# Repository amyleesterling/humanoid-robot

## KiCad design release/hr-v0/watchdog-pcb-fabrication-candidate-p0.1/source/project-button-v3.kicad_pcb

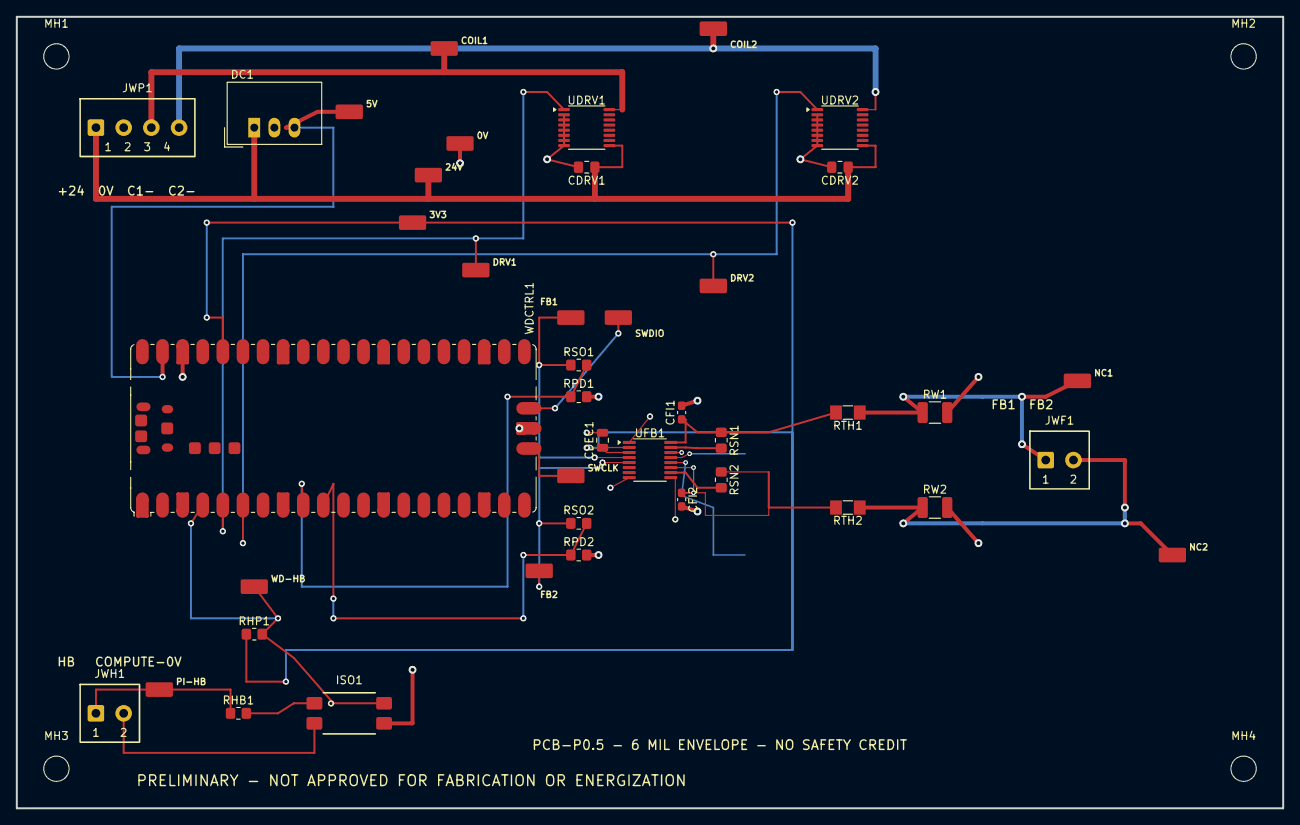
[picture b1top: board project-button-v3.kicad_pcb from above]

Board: 2 copper layers, 160.0 x 100.0 mm, 46 parts (0 on the bottom side), 24 nets.

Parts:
CDEC1: Murata GRM21BR71H104KA01L, 100 nF 50 V X7R 0805; C_0805_2012Metric
CDRV1, CDRV2: Murata GRM21BR71H104KA01L, 100 nF 50 V X7R 0805; C_0805_2012Metric_Pad1.18x1.45mm_HandSolder
CFI1, CFI2: TDK CGA3E2X7R1H103K080AA, 10 nF 50 V X7R 0603; C_0603_1608Metric_Pad1.08x0.95mm_HandSolder
DC1: TRACO POWER TSR 1-2450, 24 V to 5 V 1 A non-isola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; Converter_DCDC_TRACO_TSR-1_THT
ISO1: Vishay VO618A-4X017T heartbeat optocoupler; VO618A_Option7_SMD
JWF1: Phoenix Contact MKDS 1/2-3,5, item 1751248; MKDS_1_2_3P5
JWH1: Phoenix Contact MKDS 1/2-3,5, item 1751248; MKDS_1_2_3P5
JWP1: Phoenix Contact MKDS 1/4-3,5, item 1751264; MKDS_1_4_3P5
MH1, MH2, MH3, MH4: M3 BOARD-ONLY - MOUNTING/ENCLOSURE SELECTION OPEN; MountingHole_3.2mm_M3
RHB1: Panasonic ERJ6ENF9100V, 910 Ohm 1% 0805 0.125 W; R_0805_2012Metric_Pad1.20x1.40mm_HandSolder
RHP1: Panasonic ERJ6ENF1002V, 10.0 kOhm 1% 0805 0.125 W; R_0805_2012Metric_Pad1.20x1.40mm_HandSolder
RPD1, RPD2: Panasonic ERJ6ENF1002V, 10.0 kOhm 1% 0805; R_0805_2012Metric_Pad1.20x1.40mm_HandSolder
RSN1, RSN2: Panasonic ERJ6ENF5620V, 562 Ohm 1% 0805; R_0805_2012Metric_Pad1.20x1.40mm_HandSolder
RSO1, RSO2: Panasonic ERJ6ENF1001V, 1.00 kOhm 1% 0805; R_0805_2012Metric_Pad1.20x1.40mm_HandSolder
RTH1, RTH2: Vishay MMA02040C1001FB300, 1.00 kOhm 1% 0.4 W MELF; R_MiniMELF_MMA-0204
RW1, RW2: Vishay CRCW12102K70FKEA, 2.70 kOhm 1% 0.5 W 1210; R_1210_3225Metric_Pad1.30x2.65mm_HandSolder
TP1, TP2, TP3, TP4, TP5, TP6, TP7, TP8, TP9, TP10, TP11, TP12, TP13, TP14, TP15, TP16: Harwin S1751-46R SMT test point; Harwin_S1751_46R
UDRV1: Texas Instruments TPL7407LPWR channel-1 relay dri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; TSSOP-16_4.4x5mm_P0.65mm
UDRV2: Texas Instruments TPL7407LPWR channel-2 relay dri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; TSSOP-16_4.4x5mm_P0.65mm
UFB1: Texas Instruments ISO1212DBQ dual 24 V input rece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; SSOP-16_3.9x4.9mm_P0.635mm
WDCTRL1: Raspberry Pi Pico 1, order SC0915 / RP2040; RaspberryPi_Pico_SMD

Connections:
COMPUTE_0V: ISO1.2, JWH1.2
FB_IN1: RSN1.2, UFB1.15
FB_IN2: RSN2.2, UFB1.10
FB_SENSE1: CFI1.1, RSN1.1, RTH1.2, UFB1.16
FB_SENSE2: CFI2.1, RSN2.1, RTH2.2, UFB1.11
HB_LED_A: ISO1.1, RHB1.2
PI_HEARTBEAT: JWH1.1, RHB1.1, TP5.1
SAFETY_0V: CDEC1.2, CDRV1.2, CDRV2.2, CFI1.2, CFI2.2, DC1.2, ISO1.3, JWP1.2, RPD1.2, RPD2.2, RW1.2, RW2.2, TP2.1, UDRV1.2, UDRV1.3, UDRV1.4, UDRV1.5, UDRV1.6, UDRV1.7, UDRV1.8, UDRV2.2, UDRV2.3, UDRV2.4, UDRV2.5, UDRV2.6, UDRV2.7, UDRV2.8, UFB1.1, UFB1.8, UFB1.9, UFB1.14, WDCTRL1.38, WDCTRL1.D2
SAFETY_24V: CDRV1.1, CDRV2.1, DC1.1, JWP1.1, TP1.1, UDRV1.9, UDRV2.9
UFB_OUT1: RSO1.1, TP13.1, UFB1.4
UFB_OUT2: RSO2.1, TP14.1, UFB1.5
WD1_COIL_N: JWP1.3, TP9.1, UDRV1.16
WD1_DRIVE: TP7.1, UDRV1.1, WDCTRL1.5
WD1_NC_24V: JWF1.1, RTH1.1, RW1.1, TP11.1
WD1_NC_DIAG: RPD1.1, RSO1.2, WDCTRL1.9
WD2_COIL_N: JWP1.4, TP10.1, UDRV2.16
WD2_DRIVE: TP8.1, UDRV2.1, WDCTRL1.6
WD2_NC_24V: JWF1.2, RTH2.1, RW2.1, TP12.1
WD2_NC_DIAG: RPD2.1, RSO2.2, WDCTRL1.10
WD_3V3: CDEC1.1, RHP1.1, TP4.1, UFB1.2, UFB1.3, WDCTRL1.36
WD_5V: DC1.3, TP3.1, WDCTRL1.39
WD_HEARTBEAT: ISO1.4, RHP1.2, TP6.1, WDCTRL1.4
WD_SWCLK: TP16.1, WDCTRL1.D1
WD_SWDIO: TP15.1, WDCTRL1.D3

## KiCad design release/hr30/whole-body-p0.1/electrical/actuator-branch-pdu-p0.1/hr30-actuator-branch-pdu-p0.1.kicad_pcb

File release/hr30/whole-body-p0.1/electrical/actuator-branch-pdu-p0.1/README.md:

# HR-30 actuator branch PDU P0.1

**PRELIMINARY - NOT APPROVED FOR PROCUREMENT, FABRICATION, ASSEMBLY, CONNECTION, POWERED TESTING, MOTION OR ENERGIZATION**

This package provides one editable six-channel native KiCad schematic and routed 124 x 45 mm ten-layer PCB candidate. Five distributed assembly instances allocate 25 whole-body actuator branches and retain five DNP spares. KiCad verifies schematic ERC 0/0, PCB DRC 0/0 and zero unconnected pads. The route separates shared input, individual outputs and six control-net families; exact production stackup, copper weight, DFM, thermal rise and physical tests remain open. It is a restrained commissioning architecture only; reverse energy, connector closure, dynamic torque and all work authority remain open.

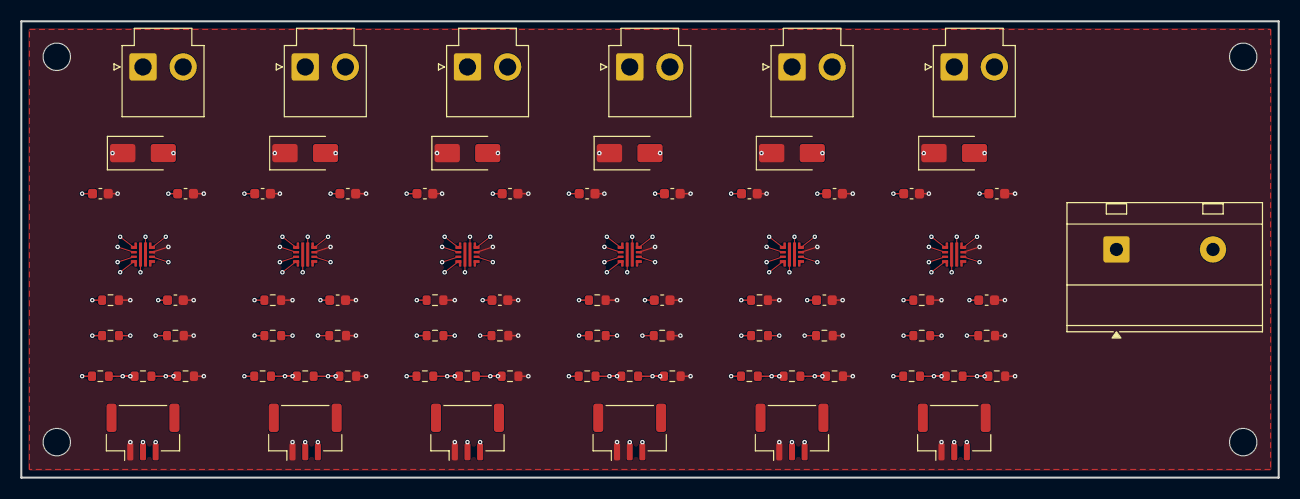
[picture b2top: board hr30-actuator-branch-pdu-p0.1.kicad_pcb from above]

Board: 10 copper layers, 124.0 x 45.0 mm, 83 parts (0 on the bottom side), 44 nets.

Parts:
C101, C201, C301, C401, C501, C601: 1uF 25V X7R input; C_0603_1608Metric
C102, C202, C302, C402, C502, C602: 2x1uF 25V X7R output equivalent; C_0603_1608Metric
C103, C203, C303, C403, C503, C603: 3.3nF dVdt; C_0603_1608Metric
D101, D201, D301, D401, D501, D601: LOCAL BRANCH CLAMP - DNP; D_SMA
J1: 12 V CONTROLLED INPUT; TerminalBlock_MetzConnect_Type703_RT10N02HGLU_1x02_P9.52mm_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
J101: CHANNEL 1 OUTPUT; JST_VH_B2P-VH_1x02_P3.96mm_Vertical
J102: CHANNEL 2 OUTPUT; JST_VH_B2P-VH_1x02_P3.96mm_Vertical
J103: CHANNEL 3 OUTPUT; JST_VH_B2P-VH_1x02_P3.96mm_Vertical
J104: CHANNEL 4 OUTPUT; JST_VH_B2P-VH_1x02_P3.96mm_Vertical
J105: CHANNEL 5 OUTPUT; JST_VH_B2P-VH_1x02_P3.96mm_Vertical
J106: CHANNEL 6 OUTPUT; JST_VH_B2P-VH_1x02_P3.96mm_Vertical
J201: CHANNEL 1 CONTROL; JST_GH_BM03B-GHS-TBT_1x03-1MP_P1.25mm_Vertical
J202: CHANNEL 2 CONTROL; JST_GH_BM03B-GHS-TBT_1x03-1MP_P1.25mm_Vertical
J203: CHANNEL 3 CONTROL; JST_GH_BM03B-GHS-TBT_1x03-1MP_P1.25mm_Vertical
J204: CHANNEL 4 CONTROL; JST_GH_BM03B-GHS-TBT_1x03-1MP_P1.25mm_Vertical
J205: CHANNEL 5 CONTROL; JST_GH_BM03B-GHS-TBT_1x03-1MP_P1.25mm_Vertical
J206: CHANNEL 6 CONTROL; JST_GH_BM03B-GHS-TBT_1x03-1MP_P1.25mm_Vertical
MH1, MH2, MH3, MH4: M2.5 BOARD-ONLY; MountingHole_2.7mm_M2.5
R101, R201, R301, R401, R501, R601: 470k 1% UVLO top; R_0603_1608Metric
R102, R202, R302, R402, R502, R602: 27.4k 1% UVLO/OVLO middle; R_0603_1608Metric
R103, R203, R303, R403, R503, R603: 40.2k 1% OVLO bottom; R_0603_1608Metric
R104, R204, R304, R404, R504, R604: 47k 1% PGTH top; R_0603_1608Metric
R105, R205, R305, R405, R505, R605: 5.76k 1% PGTH bottom; R_0603_1608Metric
R106, R206, R306, R406, R506, R606: ASSEMBLY VARIANT RILM; R_0603_1608Metric
U201, U202, U203, U204, U205, U206: TPS259474LRPWR circuit-breaker latch-off eFuse; TI_RPW0010A_HotRodQFN_2x2mm_P0.45mm_TI4225183A_P02

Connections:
BRANCH_1_12V: C102.1, D101.2, J101.2, R104.1, U201.6
BRANCH_2_12V: C202.1, D201.2, J102.2, R204.1, U202.6
BRANCH_3_12V: C302.1, D301.2, J103.2, R304.1, U203.6
BRANCH_4_12V: C402.1, D401.2, J104.2, R404.1, U204.6
BRANCH_5_12V: C502.1, D501.2, J105.2, R504.1, U205.6
BRANCH_6_12V: C602.1, D601.2, J106.2, R604.1, U206.6
CH1_DVDT: C103.1, U201.7
CH1_EN: J201.2, R101.2, R102.1, U201.1
CH1_ILM: R106.1, U201.9
CH1_OV: R102.2, R103.1, U201.2
CH1_PG: J201.3, U201.3
CH1_PGTH: R104.2, R105.1, U201.4
CH2_DVDT: C203.1, U202.7
CH2_EN: J202.2, R201.2, R202.1, U202.1
CH2_ILM: R206.1, U202.9
CH2_OV: R202.2, R203.1, U202.2
CH2_PG: J202.3, U202.3
CH2_PGTH: R204.2, R205.1, U202.4
CH3_DVDT: C303.1, U203.7
CH3_EN: J203.2, R301.2, R302.1, U203.1
CH3_ILM: R306.1, U203.9
CH3_OV: R302.2, R303.1, U203.2
CH3_PG: J203.3, U203.3
CH3_PGTH: R304.2, R305.1, U203.4
CH4_DVDT: C403.1, U204.7
CH4_EN: J204.2, R401.2, R402.1, U204.1
CH4_ILM: R406.1, U204.9
CH4_OV: R402.2, R403.1, U204.2
CH4_PG: J204.3, U204.3
CH4_PGTH: R404.2, R405.1, U204.4
CH5_DVDT: C503.1, U205.7
CH5_EN: J205.2, R501.2, R502.1, U205.1
CH5_ILM: R506.1, U205.9
CH5_OV: R502.2, R503.1, U205.2
CH5_PG: J205.3, U205.3
CH5_PGTH: R504.2, R505.1, U205.4
CH6_DVDT: C603.1, U206.7
CH6_EN: J206.2, R601.2, R602.1, U206.1
CH6_ILM: R606.1, U206.9
CH6_OV: R602.2, R603.1, U206.2
CH6_PG: J206.3, U206.3
CH6_PGTH: R604.2, R605.1, U206.4
PDU_0V: C101.2, C102.2, C103.2, C201.2, C202.2, C203.2, C301.2, C302.2, C303.2, C401.2, C402.2, C403.2, C501.2, C502.2, C503.2, C601.2, C602.2, C603.2, D101.1, D201.1, D301.1, D401.1, D501.1, D601.1, J1.1, J101.1, J102.1, J103.1, J104.1, J105.1, J106.1, J201.1, J202.1, J203.1, J204.1, J205.1, J206.1, R103.2, R105.2, R106.2, R203.2, R205.2, R206.2, R303.2, R305.2, R306.2, R403.2, R405.2, R406.2, R503.2, R505.2, R506.2, R603.2, R605.2, R606.2, U201.8, U202.8, U203.8, U204.8, U205.8, U206.8
PDU_12V_IN: C101.1, C201.1, C301.1, C401.1, C501.1, C601.1, J1.2, R101.1, R201.1, R301.1, R401.1, R501.1, R601.1, U201.5, U202.5, U203.5, U204.5, U205.5, U206.5

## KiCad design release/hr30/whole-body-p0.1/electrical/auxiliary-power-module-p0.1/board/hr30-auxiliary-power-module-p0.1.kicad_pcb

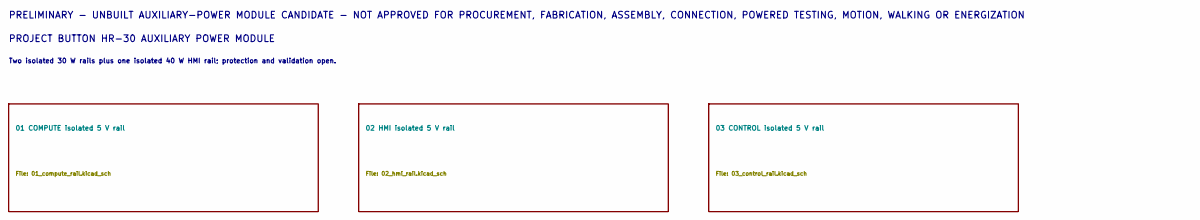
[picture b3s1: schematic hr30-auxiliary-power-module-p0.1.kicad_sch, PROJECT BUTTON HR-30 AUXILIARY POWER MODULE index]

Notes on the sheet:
PRELIMINARY - UNBUILT AUXILIARY-POWER MODULE CANDIDATE - NOT APPROVED FOR PROCUREMENT, FABRICATION, ASSEMBLY, CONNECTION, POWERED TESTING, MOTION, WALKING OR ENERGIZATION
PROJECT BUTTON HR-30 AUXILIARY POWER MODULE
Two isolated 30 W rails plus one isolated 40 W HMI rail; protection and validation open.

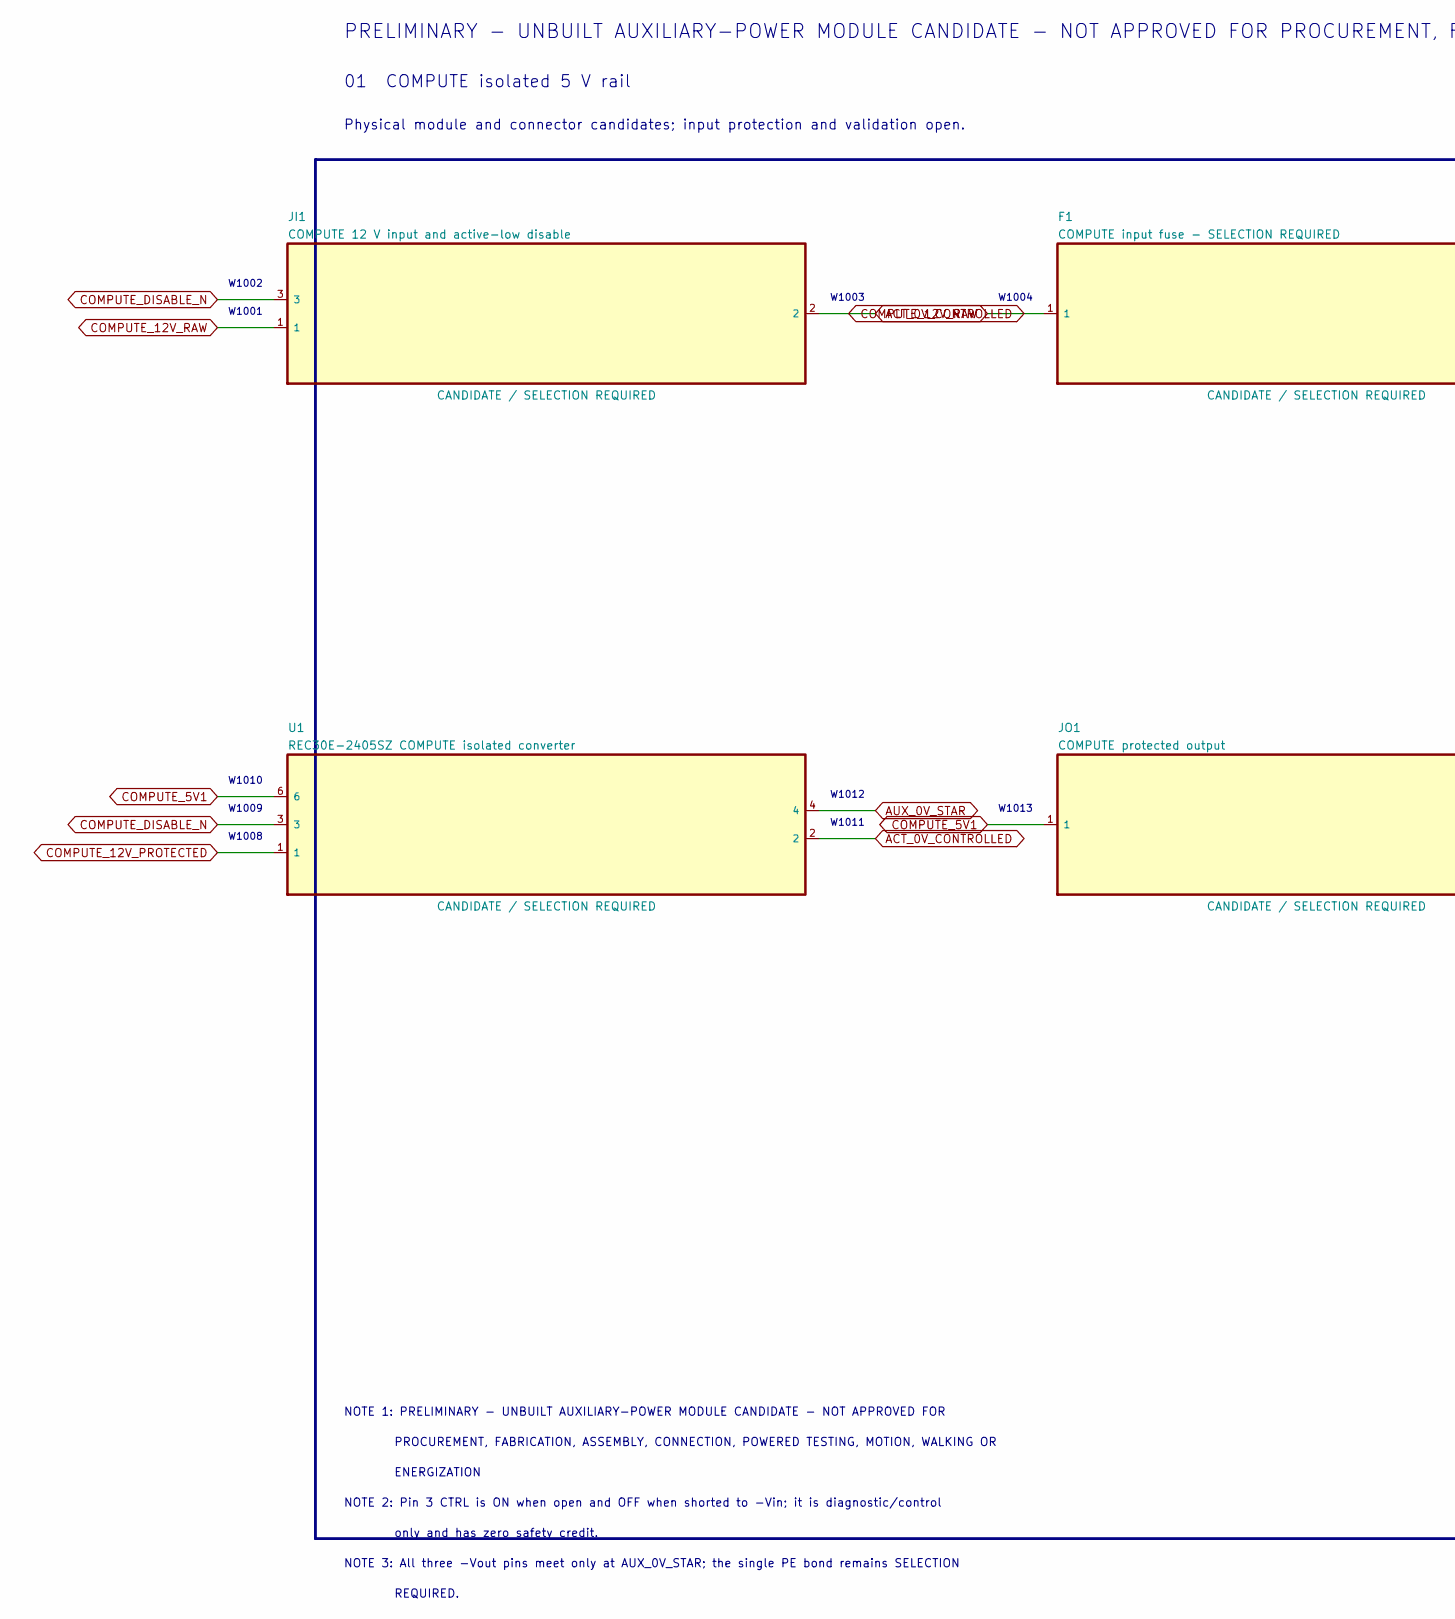
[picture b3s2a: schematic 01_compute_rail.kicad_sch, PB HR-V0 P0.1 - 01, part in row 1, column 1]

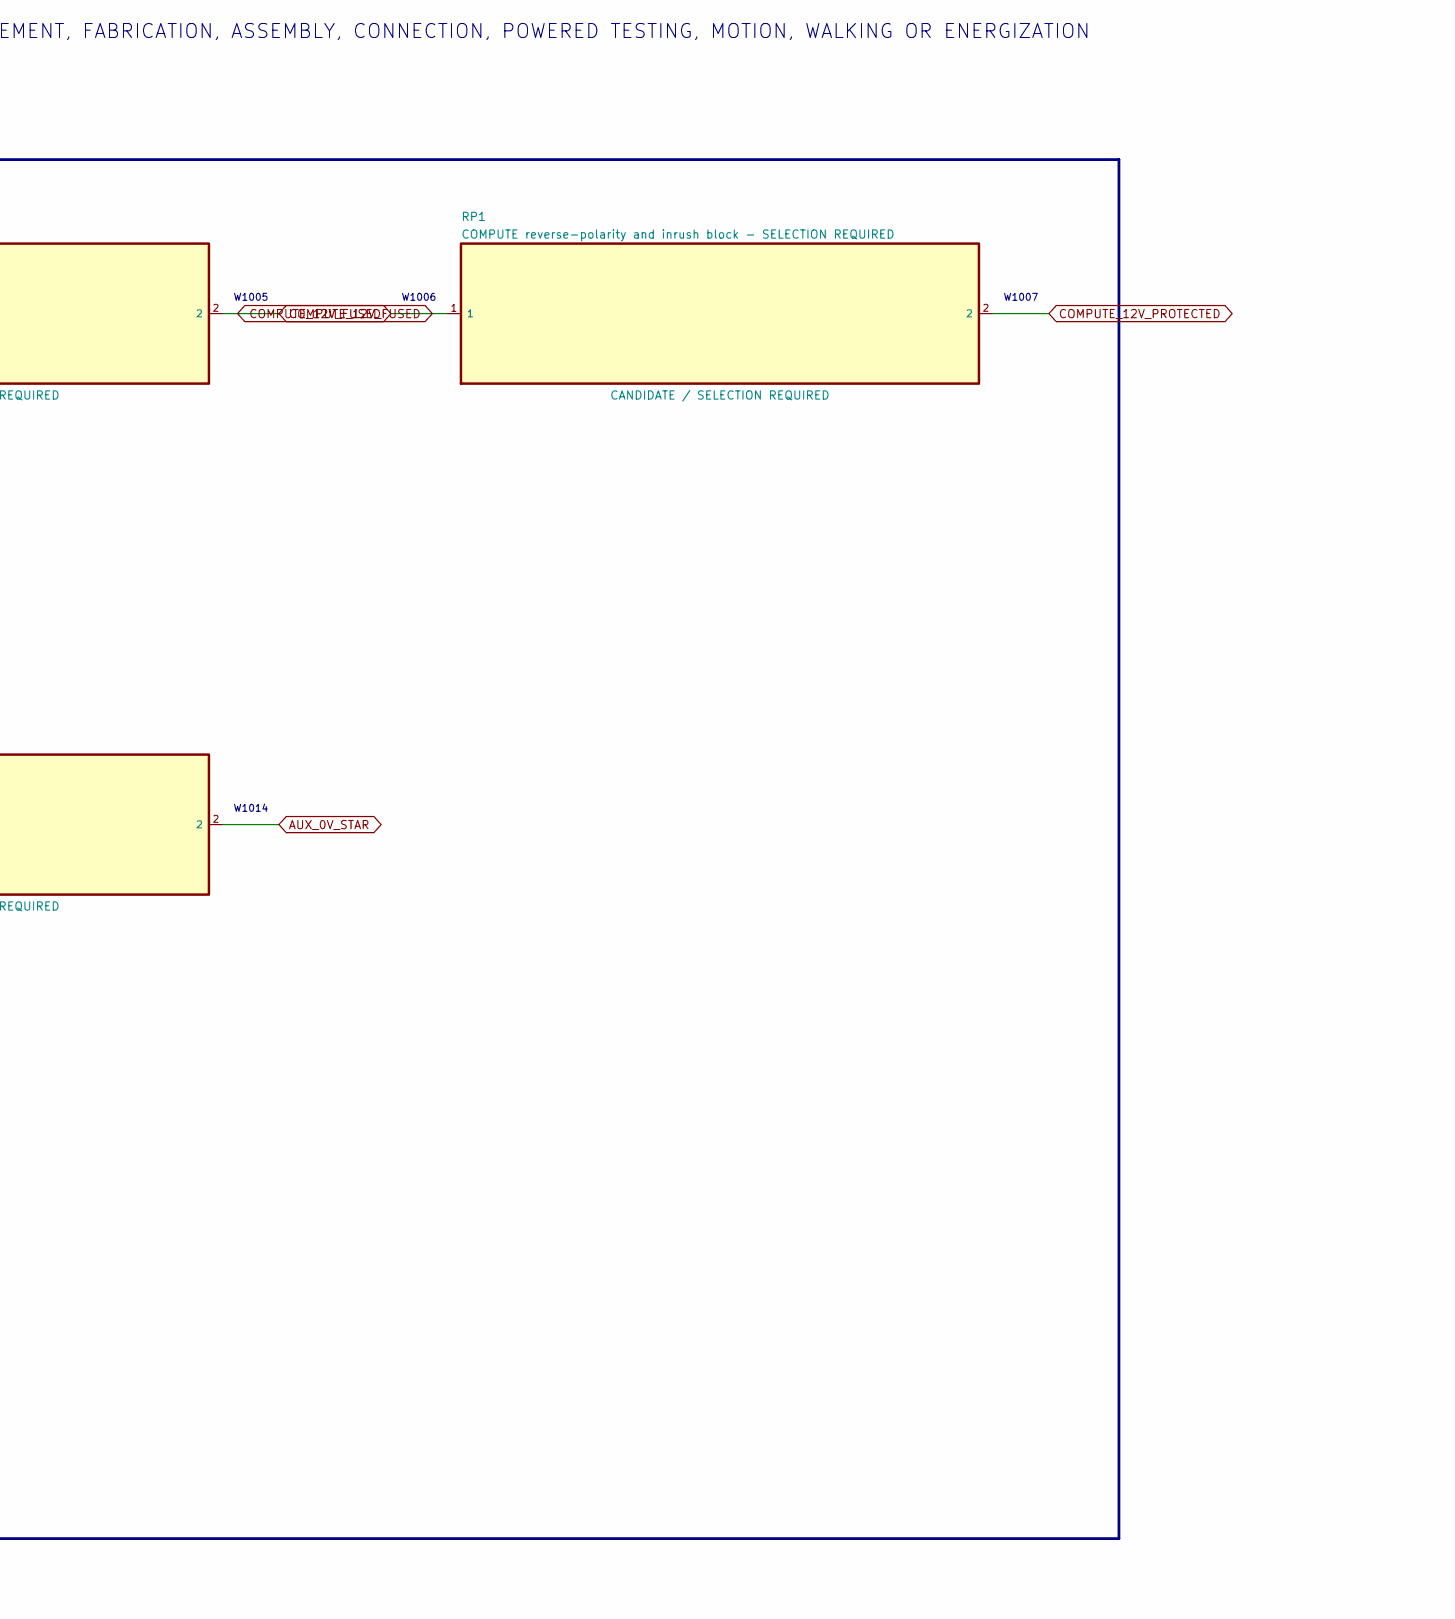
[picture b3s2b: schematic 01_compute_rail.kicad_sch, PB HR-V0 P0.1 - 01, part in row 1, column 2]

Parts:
F1: COMPUTE input fuse - SELECTION REQUIRED; AUX_SELECTION_BLOCK
JI1: COMPUTE 12 V input and active-low disable; JST_VH_B3P-VH-B_1x03_P3.96mm_Vertical
JO1: COMPUTE protected output; JST_VH_B2P-VH-B_1x02_P3.96mm_Vertical
RP1: COMPUTE reverse-polarity and inrush block - SELEC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; AUX_SELECTION_BLOCK
U1: REC30E-2405SZ COMPUTE isolated converter; REC30E-Z

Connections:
ACT_0V_CONTROLLED: JI1.2, U1.2; also elsewhere on the board
AUX_0V_STAR: JO1.2, U1.4; also elsewhere on the board
COMPUTE_5V1: JO1.1, U1.6
COMPUTE_12V_FUSED: F1.2, RP1.1
COMPUTE_12V_PROTECTED: RP1.2, U1.1
COMPUTE_12V_RAW: F1.1, JI1.1
COMPUTE_DISABLE_N: JI1.3, U1.3

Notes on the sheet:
PRELIMINARY - UNBUILT AUXILIARY-POWER MODULE CANDIDATE - NOT APPROVED FOR PROCUREMENT, FABRICATION, ASSEMBLY, CONNECTION, POWERED TESTING, MOTION, WALKING OR ENERGIZATION
01 COMPUTE isolated 5 V rail
Physical module and connector candidates; input protection and validation open.
W1001
W1002
W1003
W1004
W1005
W1006
W1007
W1008
W1009
W1010
W1011
W1012
W1013
W1014
NOTE 1: PRELIMINARY - UNBUILT AUXILIARY-POWER MODULE CANDIDATE - NOT APPROVED FOR
PROCUREMENT, FABRICATION, ASSEMBLY, CONNECTION, POWERED TESTING, MOTION, WALKING OR
ENERGIZATION
NOTE 2: Pin 3 CTRL is ON when open and OFF when shorted to -Vin; it is diagnostic/control
only and has zero safety credit.
NOTE 3: All three -Vout pins meet only at AUX_0V_STAR; the single PE bond remains SELECTION
REQUIRED.

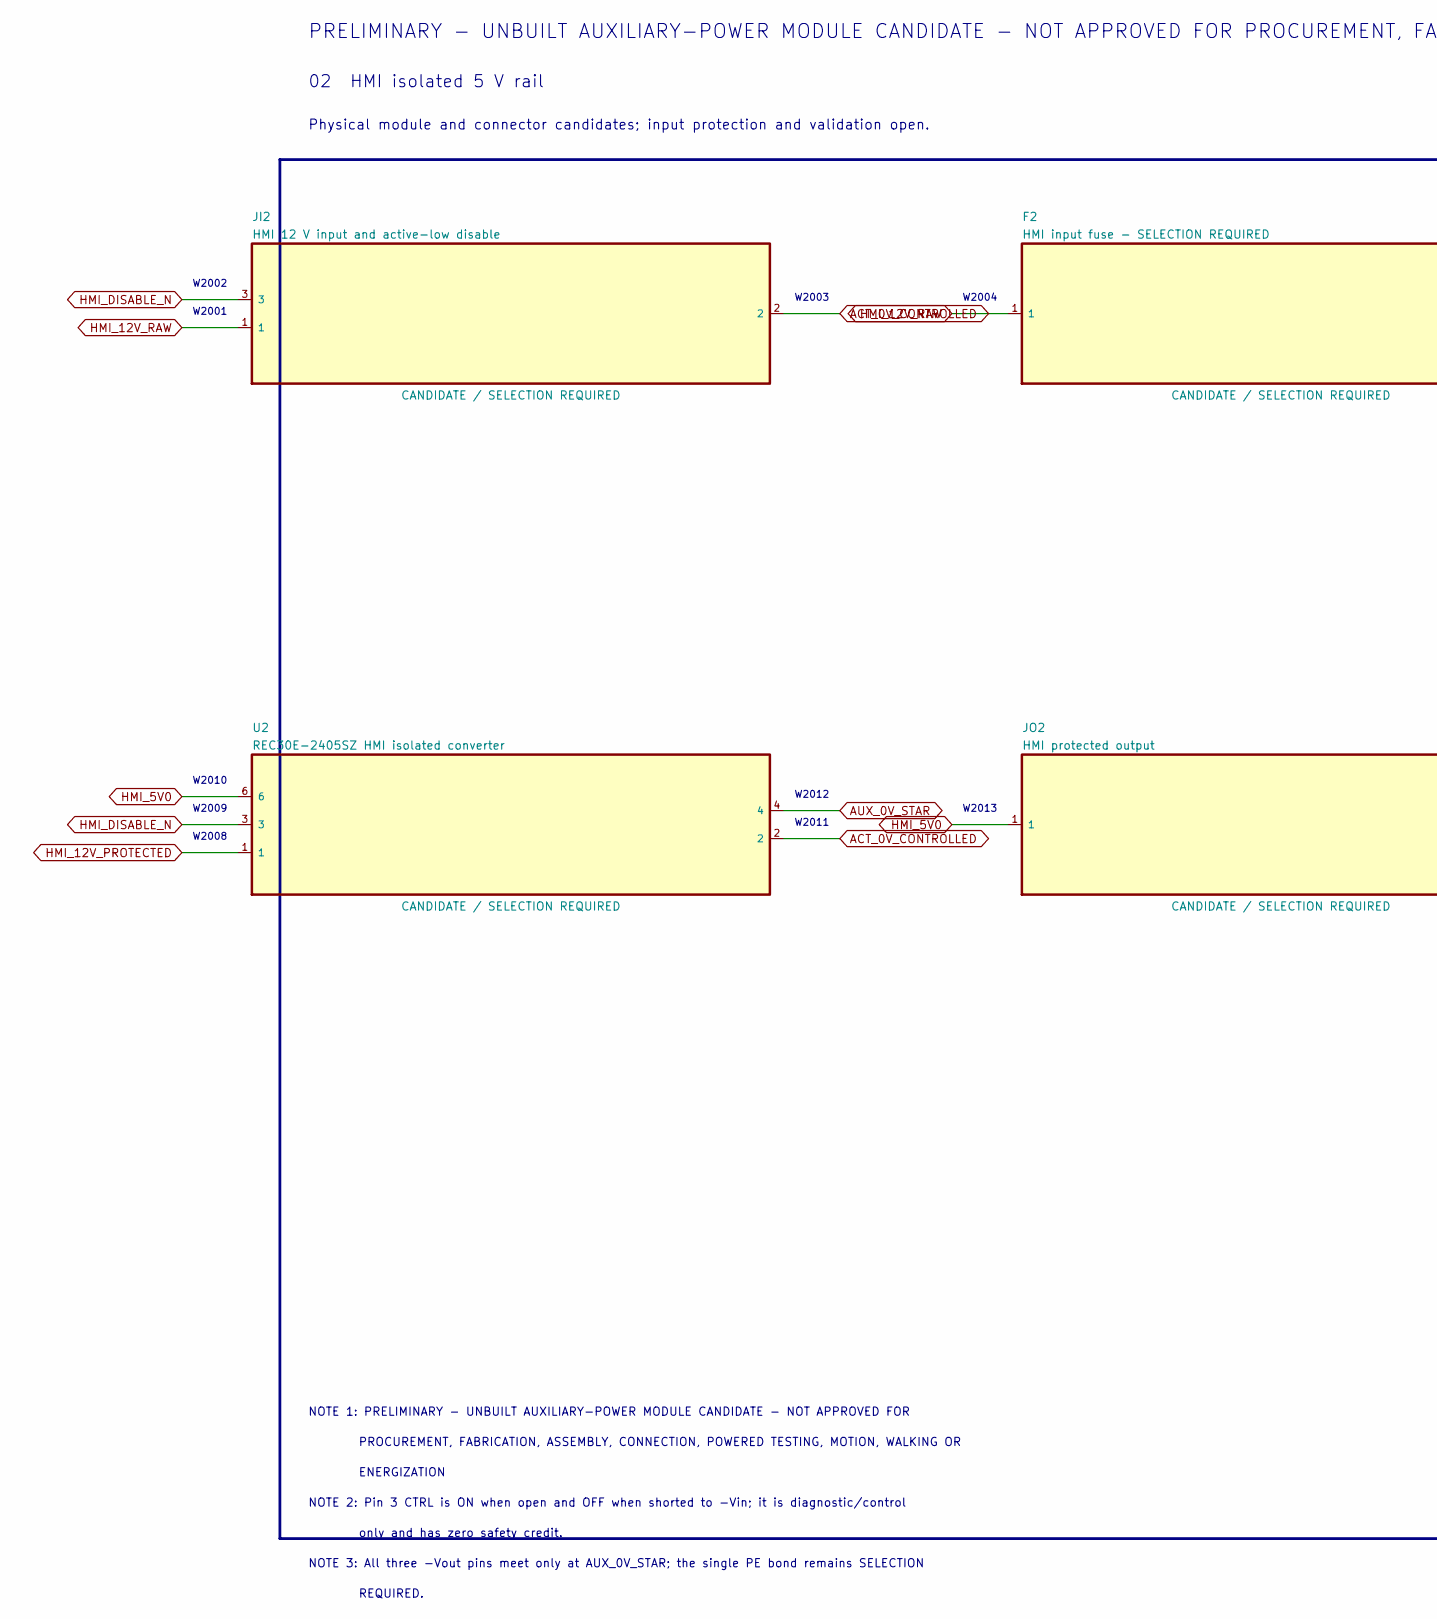
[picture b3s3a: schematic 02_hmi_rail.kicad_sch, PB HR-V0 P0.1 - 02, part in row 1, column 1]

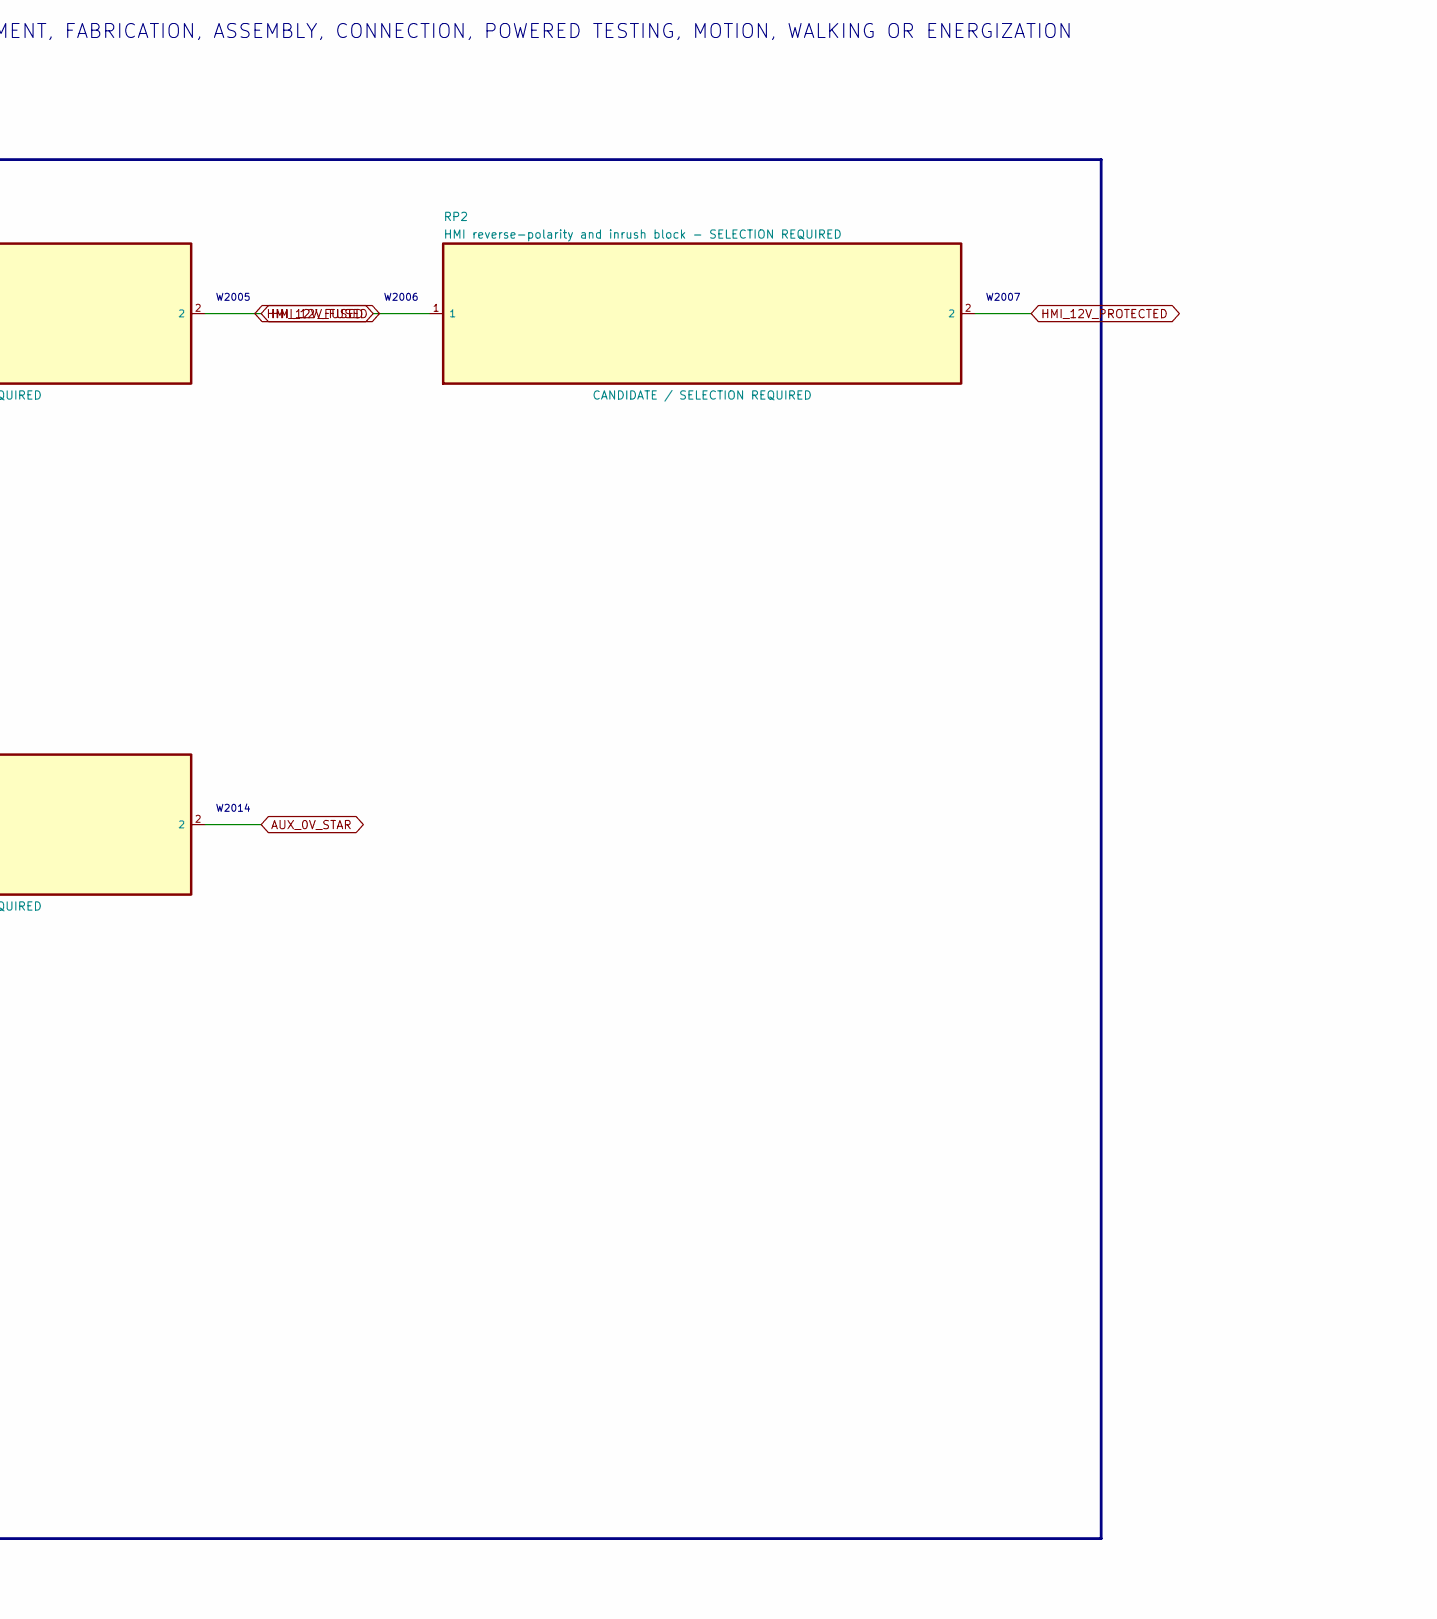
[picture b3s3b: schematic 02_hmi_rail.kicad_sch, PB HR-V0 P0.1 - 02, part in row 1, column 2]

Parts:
F2: HMI input fuse - SELECTION REQUIRED; AUX_SELECTION_BLOCK
JI2: HMI 12 V input and active-low disable; JST_VH_B3P-VH-B_1x03_P3.96mm_Vertical
JO2: HMI protected output; JST_VH_B2P-VH-B_1x02_P3.96mm_Vertical
RP2: HMI reverse-polarity and inrush block - SELECTION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; AUX_SELECTION_BLOCK
U2: REC30E-2405SZ HMI isolated converter; REC30E-Z

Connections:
ACT_0V_CONTROLLED: JI2.2, U2.2; also elsewhere on the board
AUX_0V_STAR: JO2.2, U2.4; also elsewhere on the board
HMI_5V0: JO2.1, U2.6
HMI_12V_FUSED: F2.2, RP2.1
HMI_12V_PROTECTED: RP2.2, U2.1
HMI_12V_RAW: F2.1, JI2.1
HMI_DISABLE_N: JI2.3, U2.3

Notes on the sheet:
PRELIMINARY - UNBUILT AUXILIARY-POWER MODULE CANDIDATE - NOT APPROVED FOR PROCUREMENT, FABRICATION, ASSEMBLY, CONNECTION, POWERED TESTING, MOTION, WALKING OR ENERGIZATION
02 HMI isolated 5 V rail
Physical module and connector candidates; input protection and validation open.
W2001
W2002
W2003
W2004
W2005
W2006
W2007
W2008
W2009
W2010
W2011
W2012
W2013
W2014
NOTE 1: PRELIMINARY - UNBUILT AUXILIARY-POWER MODULE CANDIDATE - NOT APPROVED FOR
PROCUREMENT, FABRICATION, ASSEMBLY, CONNECTION, POWERED TESTING, MOTION, WALKING OR
ENERGIZATION
NOTE 2: Pin 3 CTRL is ON when open and OFF when shorted to -Vin; it is diagnostic/control
only and has zero safety credit.
NOTE 3: All three -Vout pins meet only at AUX_0V_STAR; the single PE bond remains SELECTION
REQUIRED.

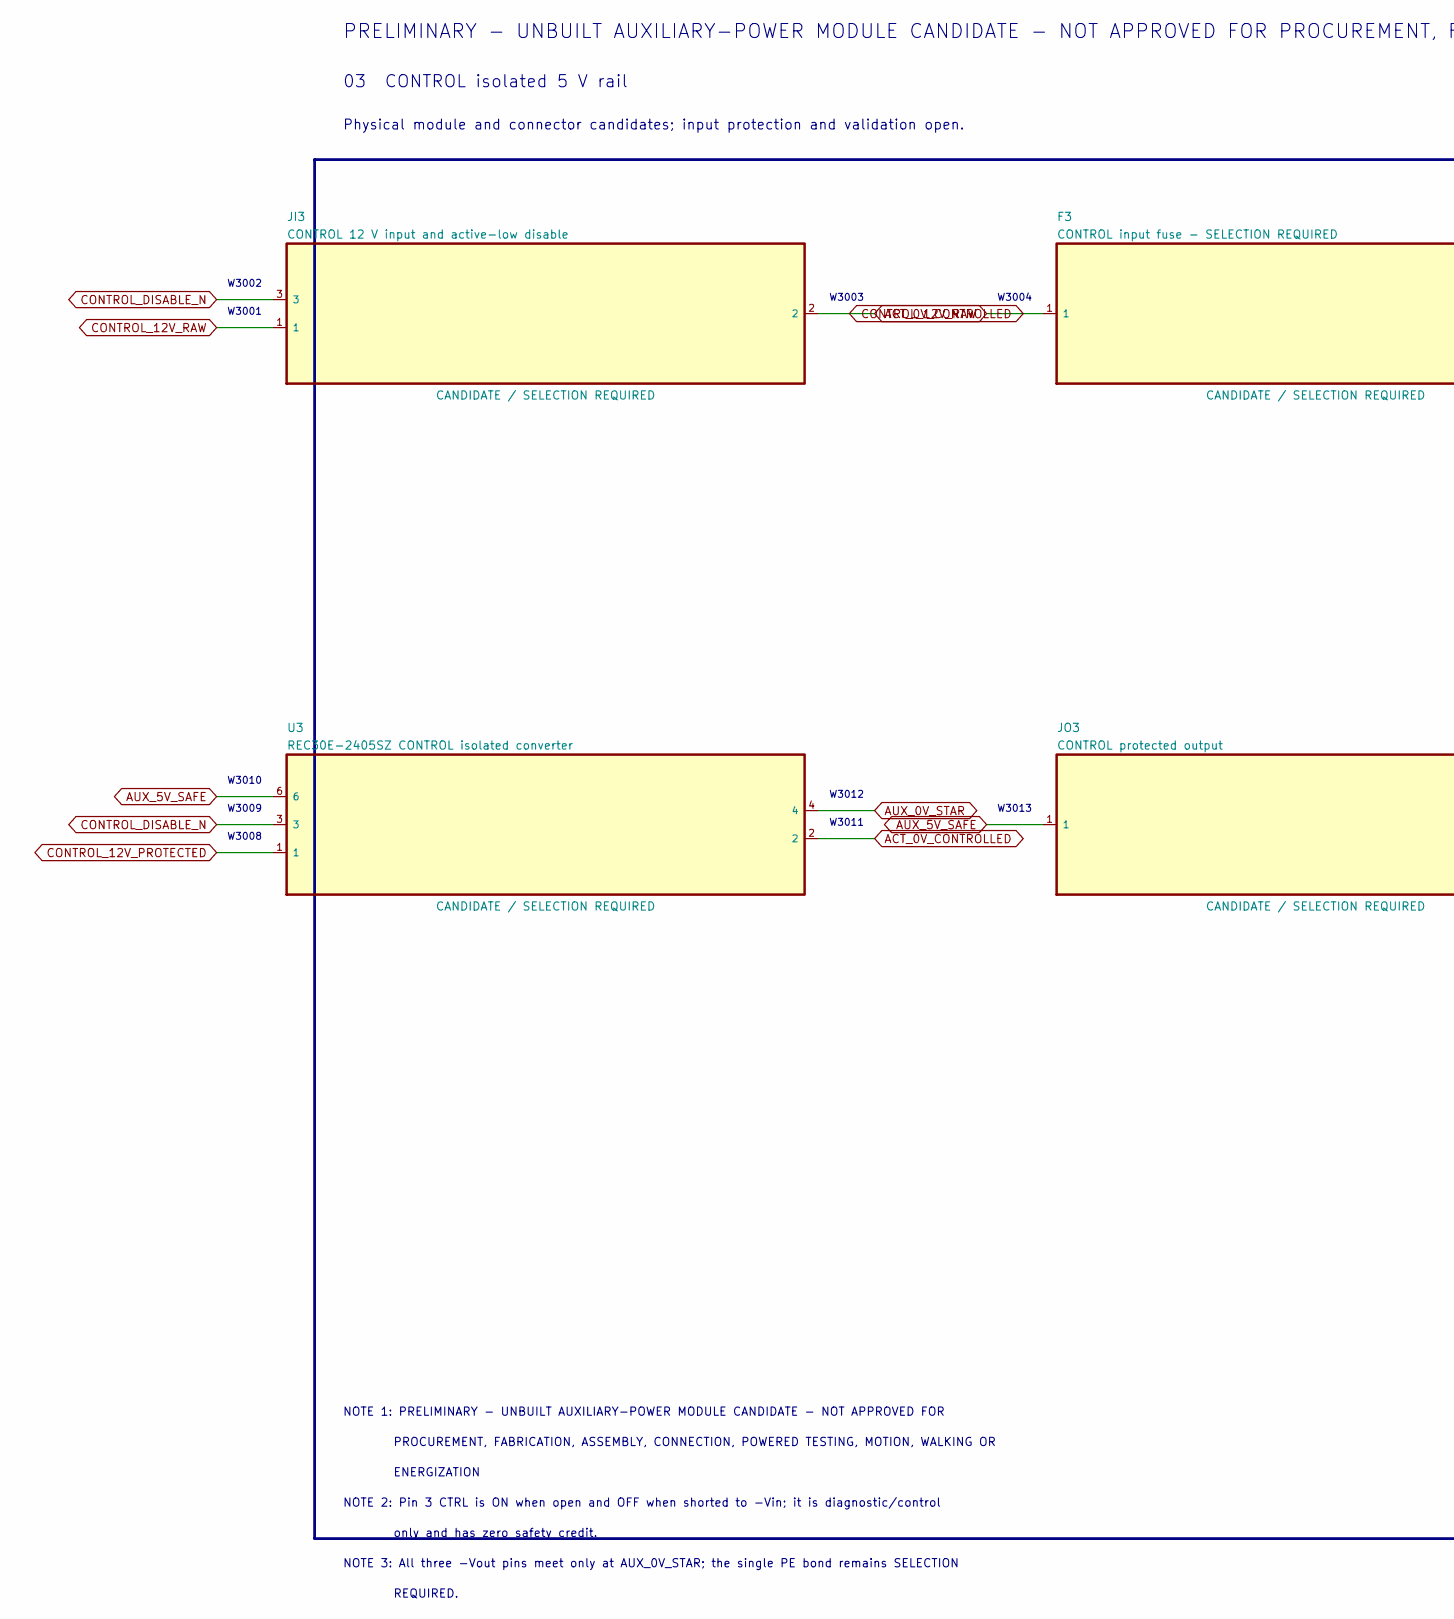
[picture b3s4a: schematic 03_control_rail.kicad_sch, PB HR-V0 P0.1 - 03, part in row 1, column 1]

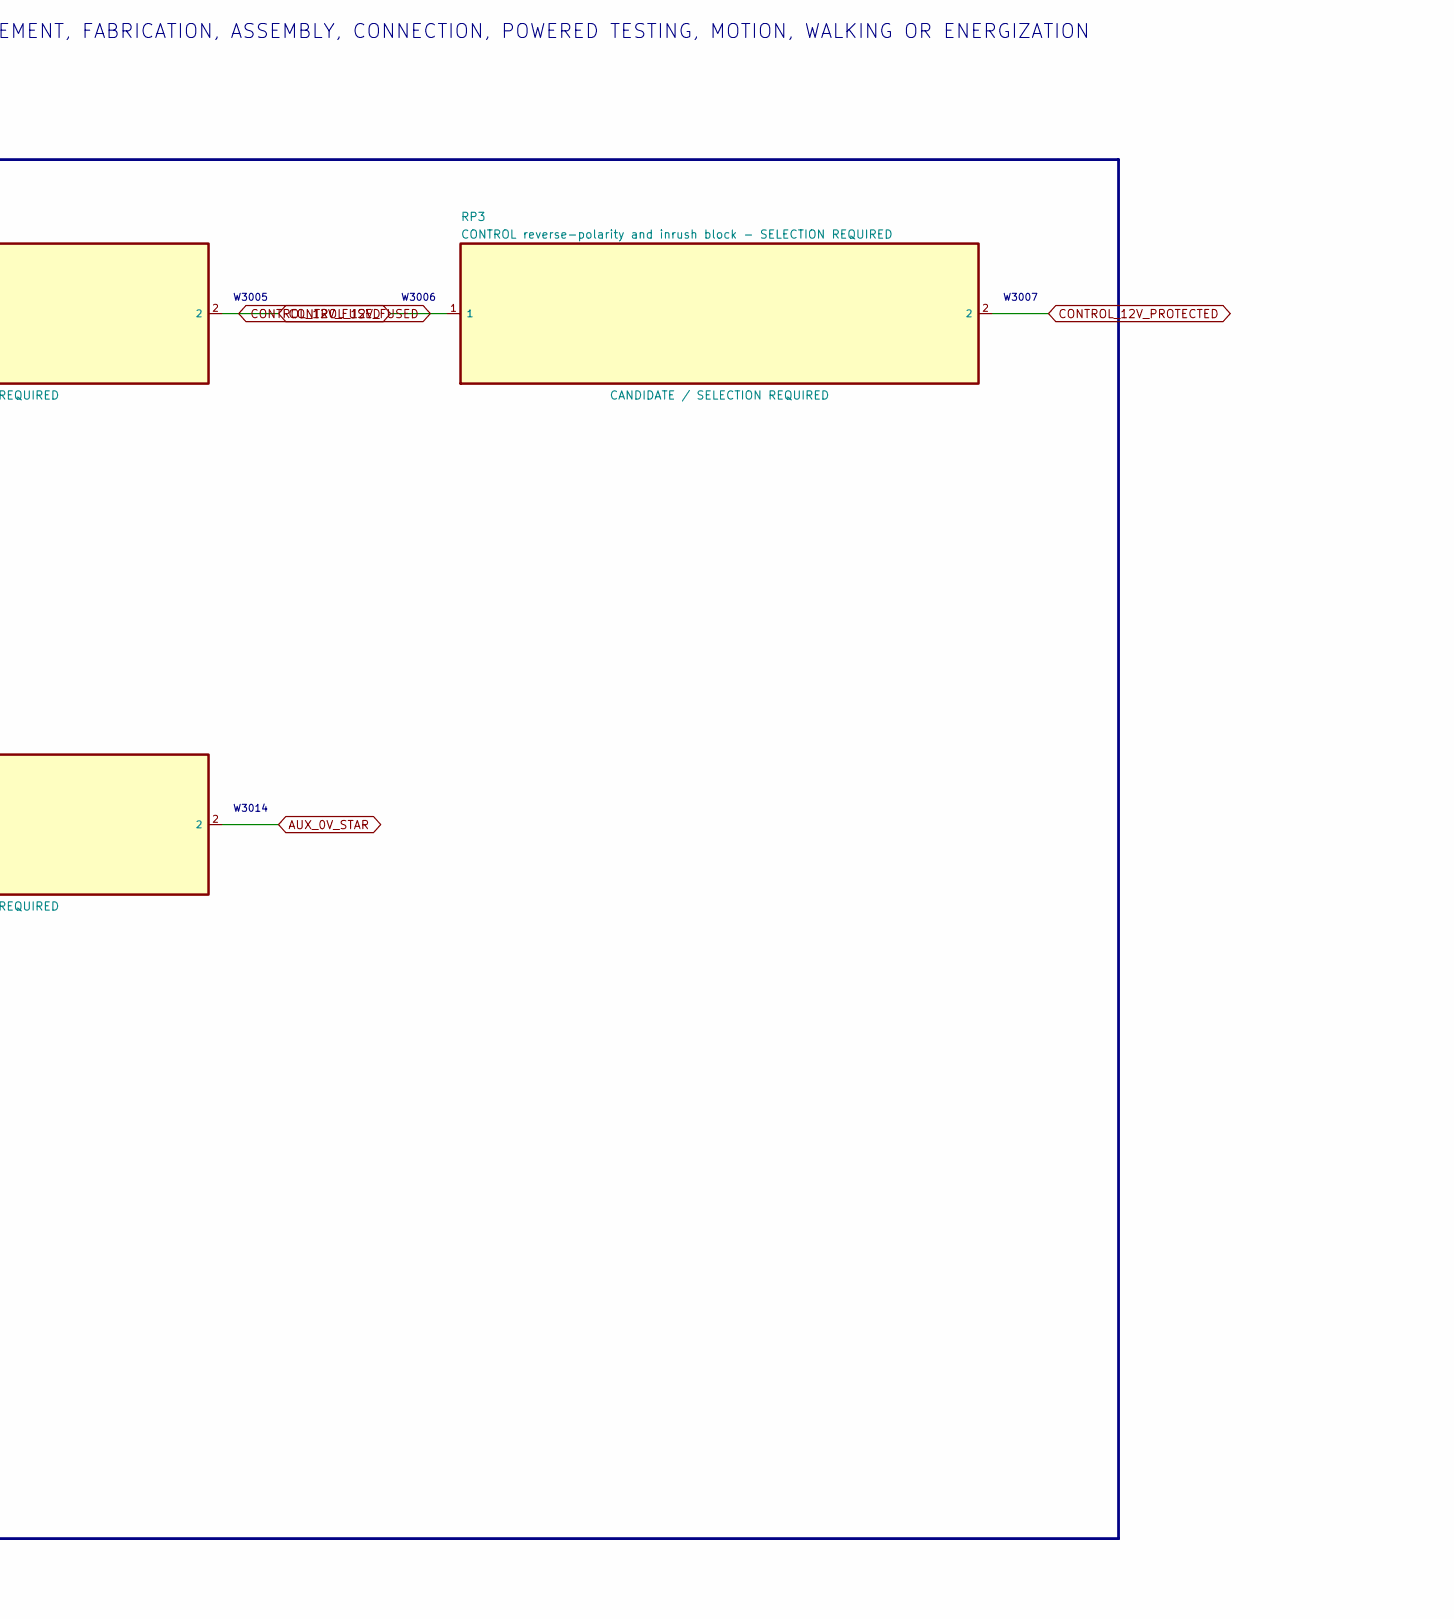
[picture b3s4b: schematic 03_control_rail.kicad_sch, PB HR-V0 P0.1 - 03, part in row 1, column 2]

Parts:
F3: CONTROL input fuse - SELECTION REQUIRED; AUX_SELECTION_BLOCK
JI3: CONTROL 12 V input and active-low disable; JST_VH_B3P-VH-B_1x03_P3.96mm_Vertical
JO3: CONTROL protected output; JST_VH_B2P-VH-B_1x02_P3.96mm_Vertical
RP3: CONTROL reverse-polarity and inrush block - SELEC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; AUX_SELECTION_BLOCK
U3: REC30E-2405SZ CONTROL isolated converter; REC30E-Z

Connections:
ACT_0V_CONTROLLED: JI3.2, U3.2; also elsewhere on the board
AUX_0V_STAR: JO3.2, U3.4; also elsewhere on the board
AUX_5V_SAFE: JO3.1, U3.6
CONTROL_12V_FUSED: F3.2, RP3.1
CONTROL_12V_PROTECTED: RP3.2, U3.1
CONTROL_12V_RAW: F3.1, JI3.1
CONTROL_DISABLE_N: JI3.3, U3.3

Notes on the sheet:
PRELIMINARY - UNBUILT AUXILIARY-POWER MODULE CANDIDATE - NOT APPROVED FOR PROCUREMENT, FABRICATION, ASSEMBLY, CONNECTION, POWERED TESTING, MOTION, WALKING OR ENERGIZATION
03 CONTROL isolated 5 V rail
Physical module and connector candidates; input protection and validation open.
W3001
W3002
W3003
W3004
W3005
W3006
W3007
W3008
W3009
W3010
W3011
W3012
W3013
W3014
NOTE 1: PRELIMINARY - UNBUILT AUXILIARY-POWER MODULE CANDIDATE - NOT APPROVED FOR
PROCUREMENT, FABRICATION, ASSEMBLY, CONNECTION, POWERED TESTING, MOTION, WALKING OR
ENERGIZATION
NOTE 2: Pin 3 CTRL is ON when open and OFF when shorted to -Vin; it is diagnostic/control
only and has zero safety credit.
NOTE 3: All three -Vout pins meet only at AUX_0V_STAR; the single PE bond remains SELECTION
REQUIRED.
